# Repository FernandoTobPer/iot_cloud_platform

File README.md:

# iot_cloud_platform
This project uses an iot platform with self made hardware (a web page made by me and a plaque).

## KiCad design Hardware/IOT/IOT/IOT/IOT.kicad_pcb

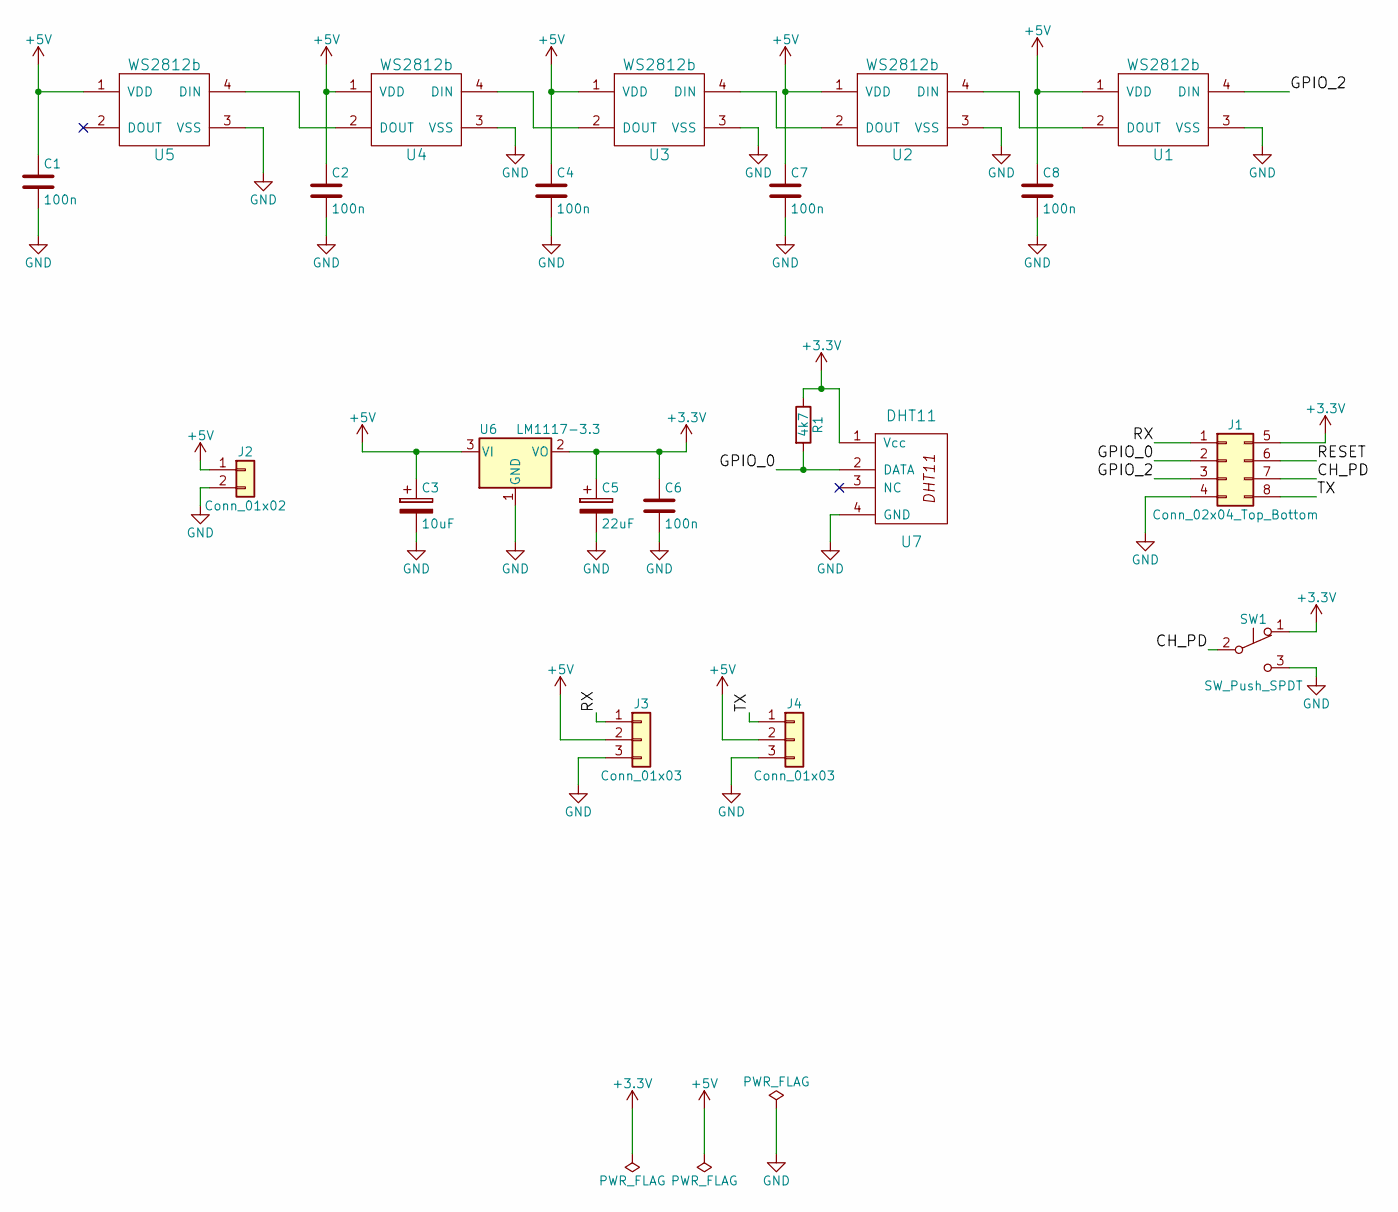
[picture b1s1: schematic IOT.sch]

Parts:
C1, C2, C4, C6, C7, C8: 100n; C_0805_HandSoldering
C3: 10uF; CP_Radial_D4.0mm_P1.50mm
C5: 22uF; CP_Radial_D4.0mm_P1.50mm
J1: Conn_02x04_Top_Bottom; Pin_Header_Straight_2x04_Pitch2.54mm
J2: Conn_01x02; Pin_Header_Straight_1x02_Pitch2.54mm
J3, J4: Conn_01x03; Pin_Header_Straight_1x03_Pitch2.54mm
R1: 4k7; R_0805_HandSoldering
SW1: SW_Push_SPDT; SW_SPDT_PCM12
U1, U2, U3, U4, U5: WS2812b; LED_WS2812B-PLCC4
U6: LM1117-3.3; SOT-223
U7: DHT11; Pin_Header_Straight_1x04_Pitch2.54mm

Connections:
+3V3: C5.1, C6.1, J1.5, R1.1, SW1.1 (A), U6.2 (VO), U7.1 (Vcc)
+5V: C1.1, C2.1, C3.1, C4.1, C7.1, C8.1, J2.1, J3.2, J4.2, U1.1 (VDD), U2.1 (VDD), U3.1 (VDD), U4.1 (VDD), U5.1 (VDD), U6.3 (VI)
/CH_PD: J1.7, SW1.2 (B)
/GPIO_0: J1.2, R1.2, U7.2 (DATA)
/GPIO_2: J1.3, U1.4 (DIN)
/RESET: J1.6
/RX: J1.1, J3.1
/TX: J1.8, J4.1
GND: C1.2, C2.2, C3.2, C4.2, C5.2, C6.2, C7.2, C8.2, J1.4, J2.2, J3.3, J4.3, SW1.3 (C), U1.3 (VSS), U2.3 (VSS), U3.3 (VSS), U4.3 (VSS), U5.3 (VSS), U6.1 (GND), U7.4 (GND)
unnamed: U1.2 (DOUT), U2.4 (DIN)
unnamed: U2.2 (DOUT), U3.4 (DIN)
unnamed: U3.2 (DOUT), U4.4 (DIN)
unnamed: U4.2 (DOUT), U5.4 (DIN)

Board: 2 copper layers, 21 parts (0 on the bottom side), 12 nets, no tracks yet.

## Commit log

2018-02-24 Basic structure setup
    Index.php linked with js and css files.
2018-03-03 I have been drawing my plaque sketch and I have also created two new components.
2018-03-17 I have created the board, it's almost finished. I only have to route it.
